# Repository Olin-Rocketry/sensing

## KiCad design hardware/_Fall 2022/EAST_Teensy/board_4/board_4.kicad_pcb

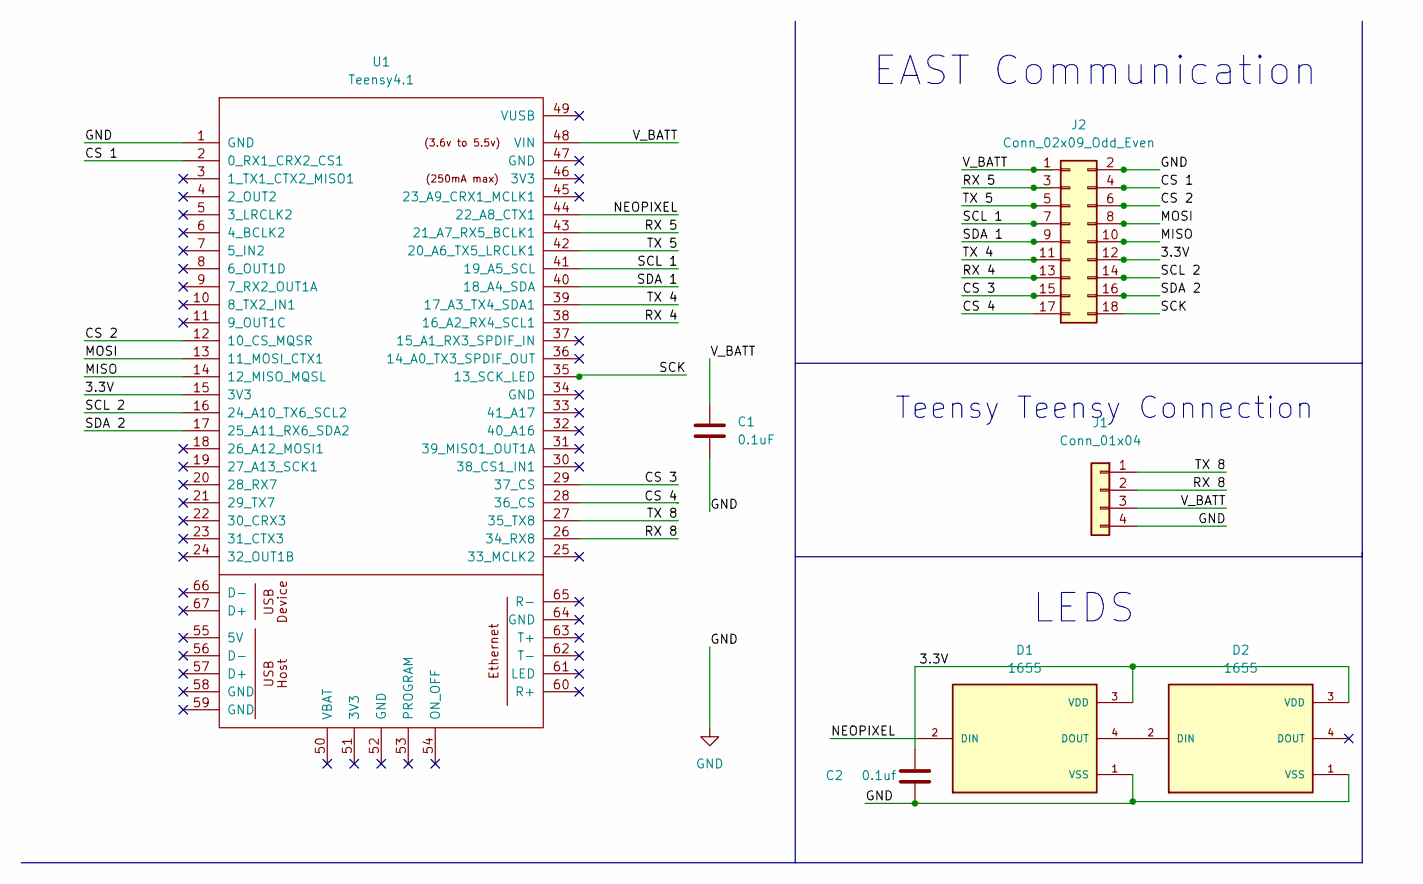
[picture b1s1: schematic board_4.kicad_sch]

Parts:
C1: 0.1uF; C_0603_1608Metric
C2: 0.1uf; C_0603_1608Metric
D1, D2: 1655; LED_1655; PARTREV 01
J1: Conn_01x04; JST_PH_S4B-PH-K_1x04_P2.00mm_Horizontal
J2: Conn_02x09_Odd_Even; PinHeader_2x09_P2.54mm_Vertical
U1: Teensy4.1; Teensy41

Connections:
/3.3V: C2.2, D1.3 (VDD), D2.3 (VDD), J2.12, U1.15 (3V3)
/CS 1: J2.4, U1.2 (0_RX1_CRX2_CS1)
/CS 2: J2.6, U1.12 (10_CS_MQSR)
/CS 3: J2.15, U1.29 (37_CS)
/CS 4: J2.17, U1.28 (36_CS)
/MISO: J2.10, U1.14 (12_MISO_MQSL)
/MOSI: J2.8, U1.13 (11_MOSI_CTX1)
/NEOPIXEL: D1.2 (DIN), U1.44 (22_A8_CTX1)
/RX 4: J2.13, U1.38 (16_A2_RX4_SCL1)
/RX 5: J2.3, U1.43 (21_A7_RX5_BCLK1)
/RX 8: J1.2, U1.26 (34_RX8)
/SCK: J2.18, U1.35 (13_SCK_LED)
/SCL 1: J2.7, U1.41 (19_A5_SCL)
/SCL 2: J2.14, U1.16 (24_A10_TX6_SCL2)
/SDA 1: J2.9, U1.40 (18_A4_SDA)
/SDA 2: J2.16, U1.17 (25_A11_RX6_SDA2)
/TX 4: J2.11, U1.39 (17_A3_TX4_SDA1)
/TX 5: J2.5, U1.42 (20_A6_TX5_LRCLK1)
/TX 8: J1.1, U1.27 (35_TX8)
/V_BATT: C1.1, J1.3, J2.1, U1.48 (VIN)
GND: C1.2, C2.1, D1.1 (VSS), D2.1 (VSS), J1.4, J2.2, U1.1 (GND)
unnamed: D1.4 (DOUT), D2.2 (DIN)

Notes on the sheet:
LEDS
Teensy Teensy Connection
EAST Communication

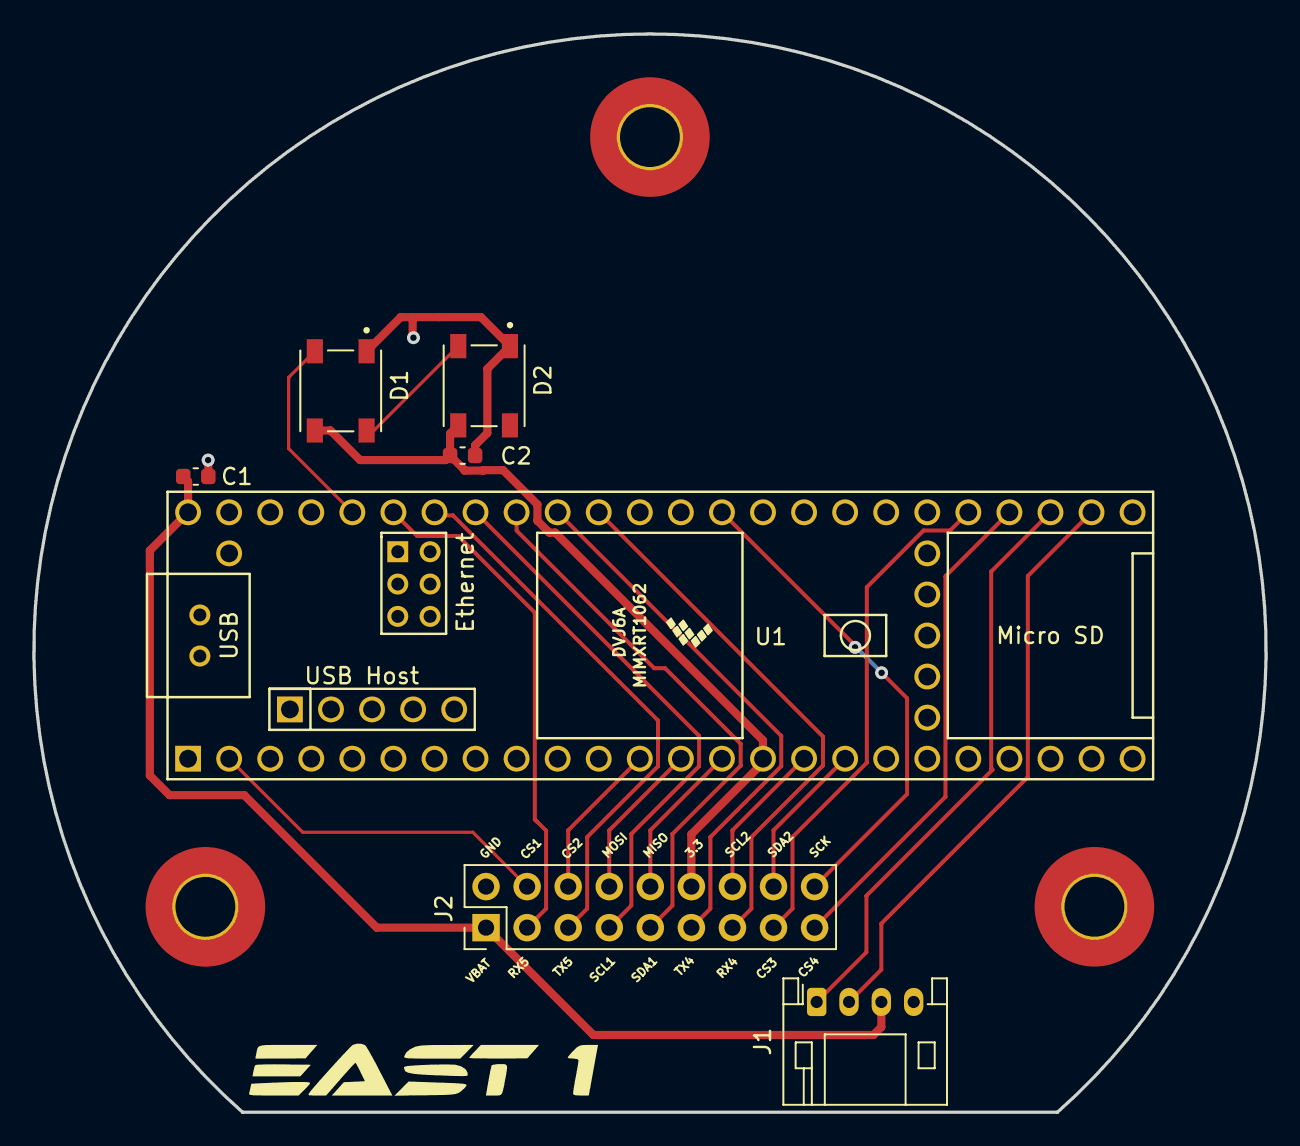
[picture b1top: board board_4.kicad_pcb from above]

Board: 2 copper layers, 76.2 x 66.7 mm, 7 parts (0 on the bottom side), 22 nets.

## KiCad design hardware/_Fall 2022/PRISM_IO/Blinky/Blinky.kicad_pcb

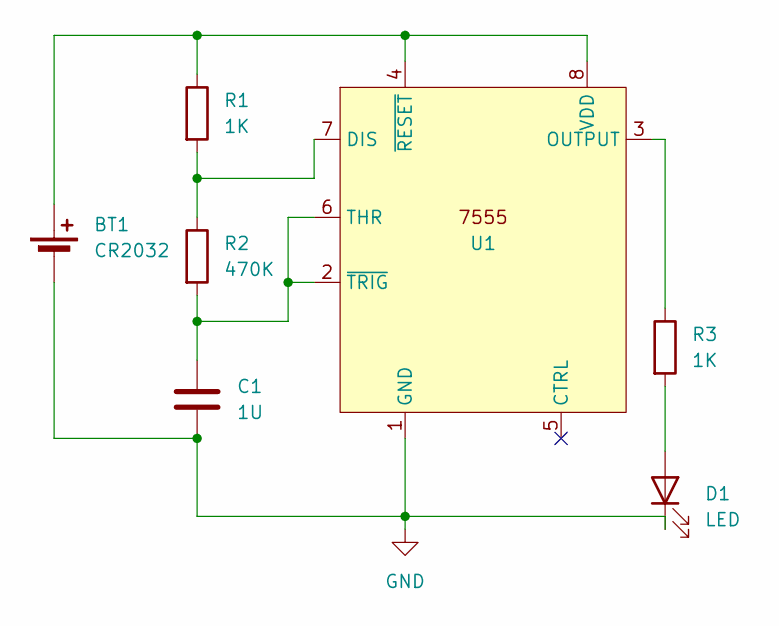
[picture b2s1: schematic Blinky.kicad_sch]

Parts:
BT1: CR2032; S8211-46R
C1: 1U; C_0805_2012Metric_Pad1.18x1.45mm_HandSolder
D1: LED; LED_0805_2012Metric_Pad1.15x1.40mm_HandSolder
R1, R3: 1K; R_0805_2012Metric_Pad1.20x1.40mm_HandSolder
R2: 470K; R_0805_2012Metric_Pad1.20x1.40mm_HandSolder
U1: SOIC-8_3.9x4.9mm_P1.27mm

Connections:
GND: BT1.2 (-), C1.2, D1.1 (K), U1.1 (GND)
unnamed: BT1.1 (+), R1.1, U1.4 (~RESET), U1.8 (VDD)
unnamed: D1.2 (A), R3.2
unnamed: R1.2, R2.1, U1.7 (DIS)
unnamed: R3.1, U1.3 (OUTPUT)
unnamed: C1.1, R2.2, U1.2 (~TRIG), U1.6 (THR)

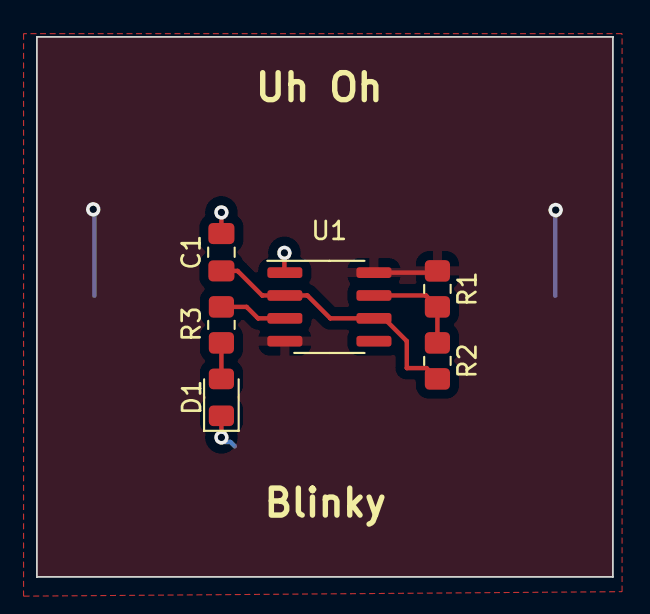
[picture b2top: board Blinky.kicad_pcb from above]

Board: 2 copper layers, 32.0 x 30.0 mm, 7 parts (1 on the bottom side), 6 nets.

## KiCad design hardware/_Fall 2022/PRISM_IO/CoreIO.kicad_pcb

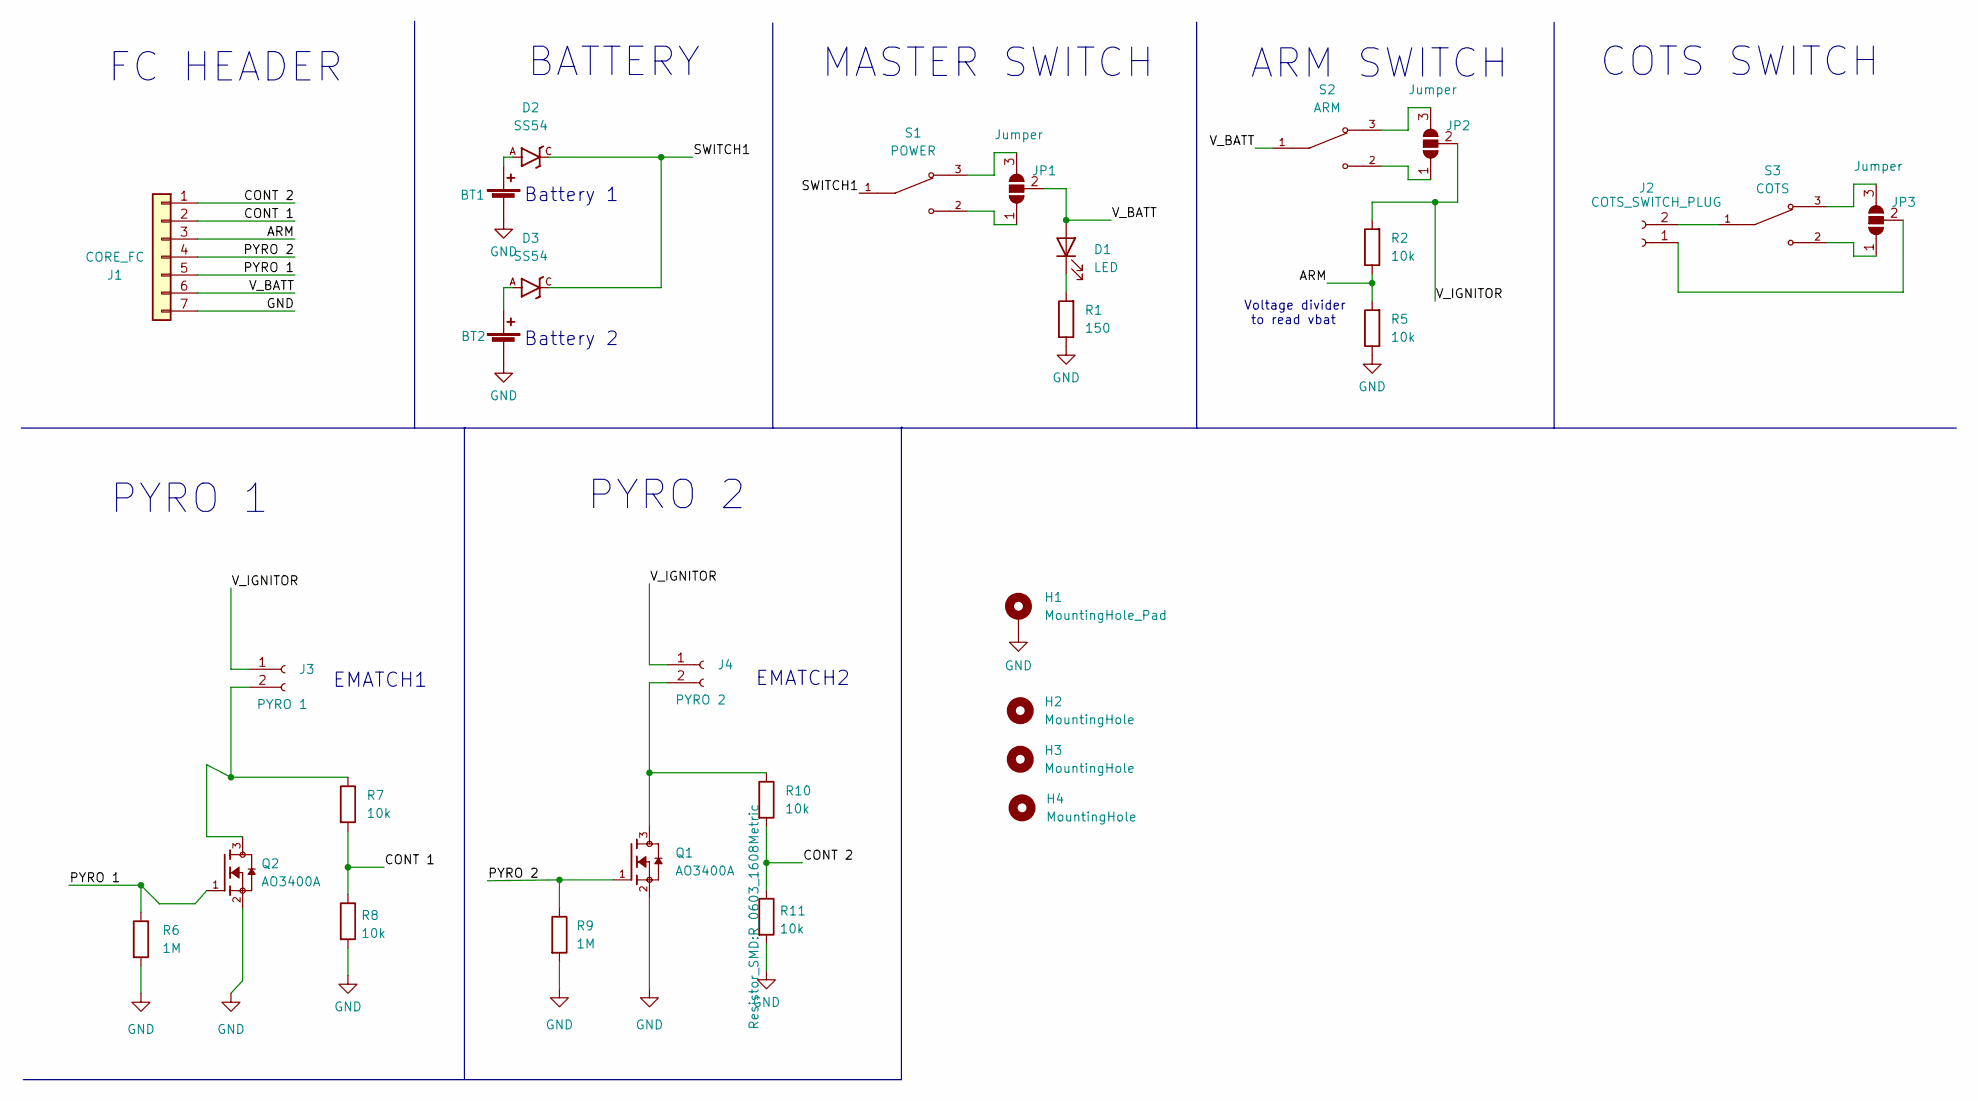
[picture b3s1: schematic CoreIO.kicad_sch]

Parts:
BT1, BT2: JST_SFH_SM02B-SFHRS-TF_02x1.80mm_Angled
D1: LED; LED_0603_1608Metric
D2, D3: SS54; DO-214AC
H1: MountingHole_Pad; MountingHole_3.2mm_M3_DIN965_Pad_TopBottom
H2, H3, H4: MountingHole; MountingHole_3.2mm_M3_DIN965_Pad_TopBottom
J1: CORE_FC; JST_PH_S7B-PH-K_1x07_P2.00mm_Horizontal
J2: COTS_SWITCH_PLUG; JST_PH_S2B-PH-K_1x02_P2.00mm_Horizontal
J3: PYRO 1; JST_SFH_SM02B-SFHRS-TF_02x1.80mm_Angled
J4: PYRO 2; JST_SFH_SM02B-SFHRS-TF_02x1.80mm_Angled
JP1, JP2, JP3: Jumper; SolderJumper-3_P1.3mm_Open_Pad1.0x1.5mm_NumberLabels
Q1, Q2: AO3400A; SOT95P280X125-3N; PARTREV L
R1: 150; R_0603_1608Metric
R2, R5, R7, R8, R10, R11: 10k; R_0603_1608Metric
R6, R9: 1M; R_0603_1608Metric
S1: POWER; SW_D2F-01F; PARTREV B036-E1-12
S2: ARM; SW_D2F-01F; PARTREV B036-E1-12
S3: COTS; SW_D2F-01F; PARTREV B036-E1-12

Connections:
/ARM: J1.3, R2.1, R5.2
/CONT 1: J1.2, R7.2, R8.1
/CONT 2: J1.1, R10.2, R11.1
/PYRO 1: J1.5, Q2.1, R6.1
/PYRO 2: J1.4, Q1.1, R9.1
/SWITCH1: D2.C, D3.C, S1.1
/V_BATT: D1.2 (A), J1.6, JP1.2 (C), S2.1
/V_IGNITOR: J3.1, J4.1, JP2.2 (C), R2.2
GND: BT1.2 (-), BT2.2 (-), H1.1, J1.7, Q1.2, Q2.2, R1.1, R5.1, R6.2, R8.2, R9.2, R11.2
unnamed: BT1.1 (+), D2.A
unnamed: BT2.1 (+), D3.A
unnamed: D1.1 (K), R1.2
unnamed: J2.1, JP3.2 (C)
unnamed: J2.2, S3.1
unnamed: J3.2, Q2.3, R7.1
unnamed: J4.2, Q1.3, R10.1
unnamed: JP1.1 (A), S1.2
unnamed: JP1.3 (B), S1.3
unnamed: JP2.1 (A), S2.2
unnamed: JP2.3 (B), S2.3
unnamed: JP3.1 (A), S3.2
unnamed: JP3.3 (B), S3.3

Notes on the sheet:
ARM SWITCH
EMATCH1
PYRO 1
BATTERY
EMATCH2
Voltage divider to read vbat
MASTER SWITCH
PYRO 2
Battery 2
FC HEADER
COTS SWITCH
Battery 1

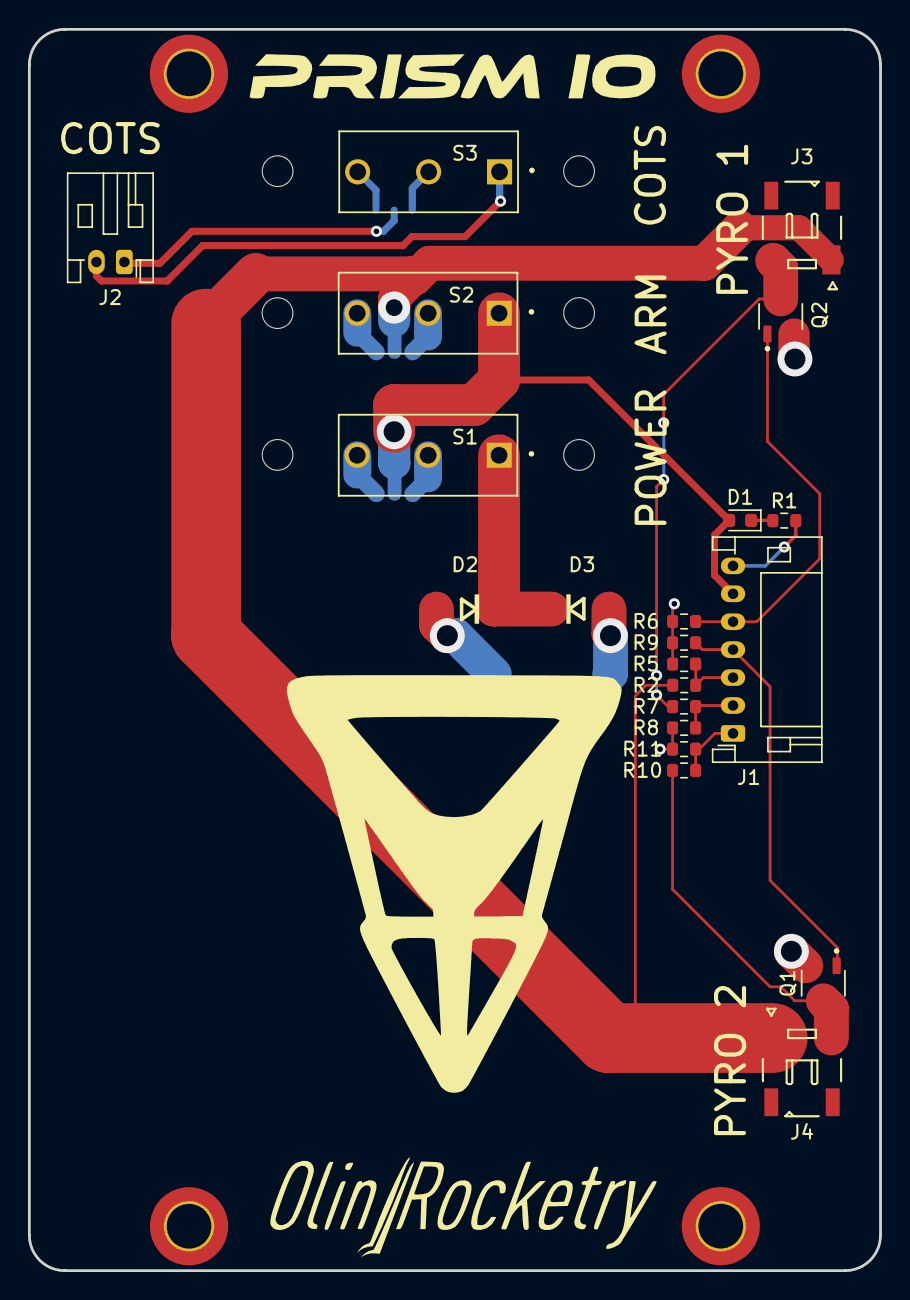
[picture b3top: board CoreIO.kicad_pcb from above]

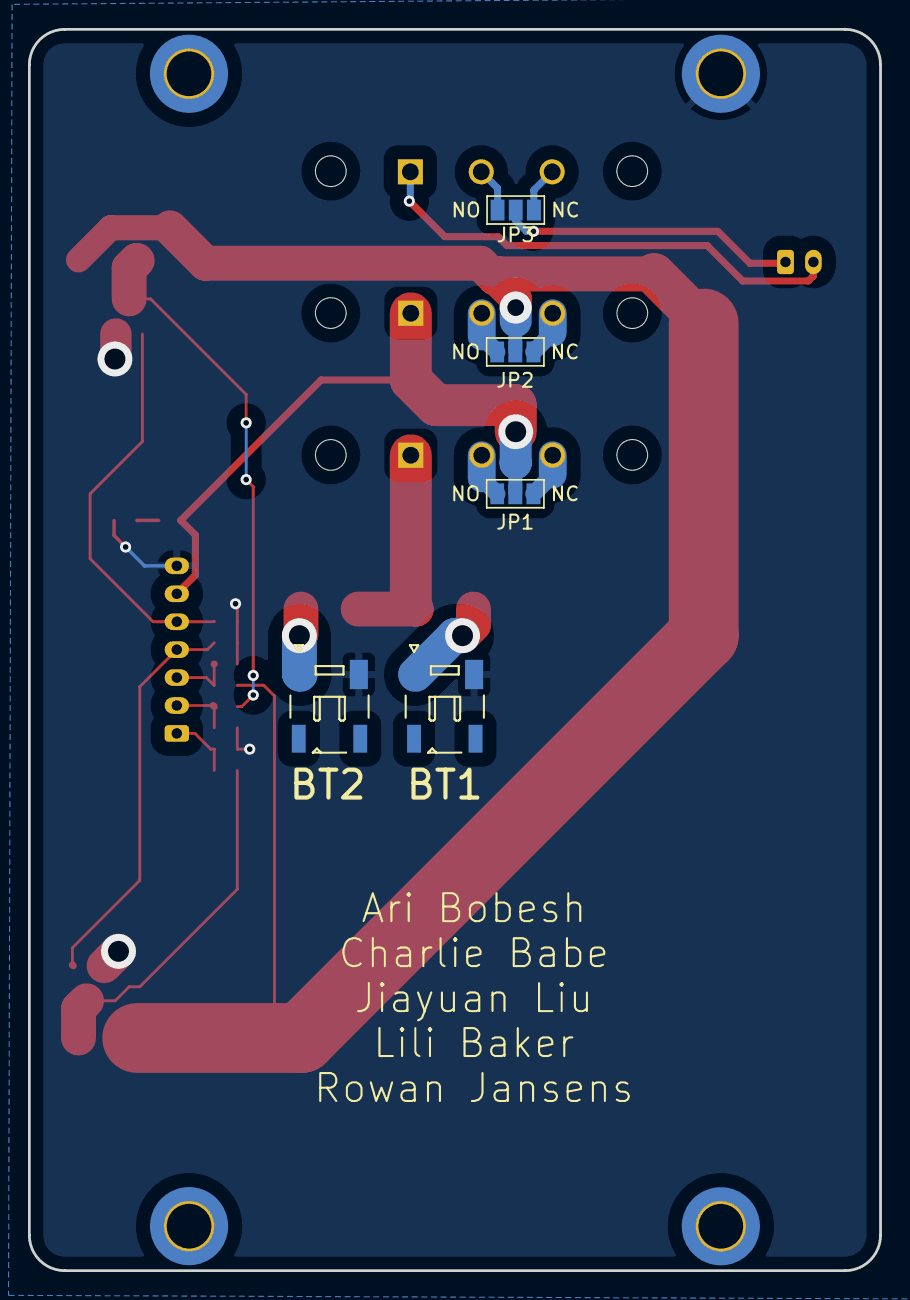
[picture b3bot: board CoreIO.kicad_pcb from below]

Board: 2 copper layers, 61.0 x 88.9 mm, 30 parts (5 on the bottom side), 22 nets.

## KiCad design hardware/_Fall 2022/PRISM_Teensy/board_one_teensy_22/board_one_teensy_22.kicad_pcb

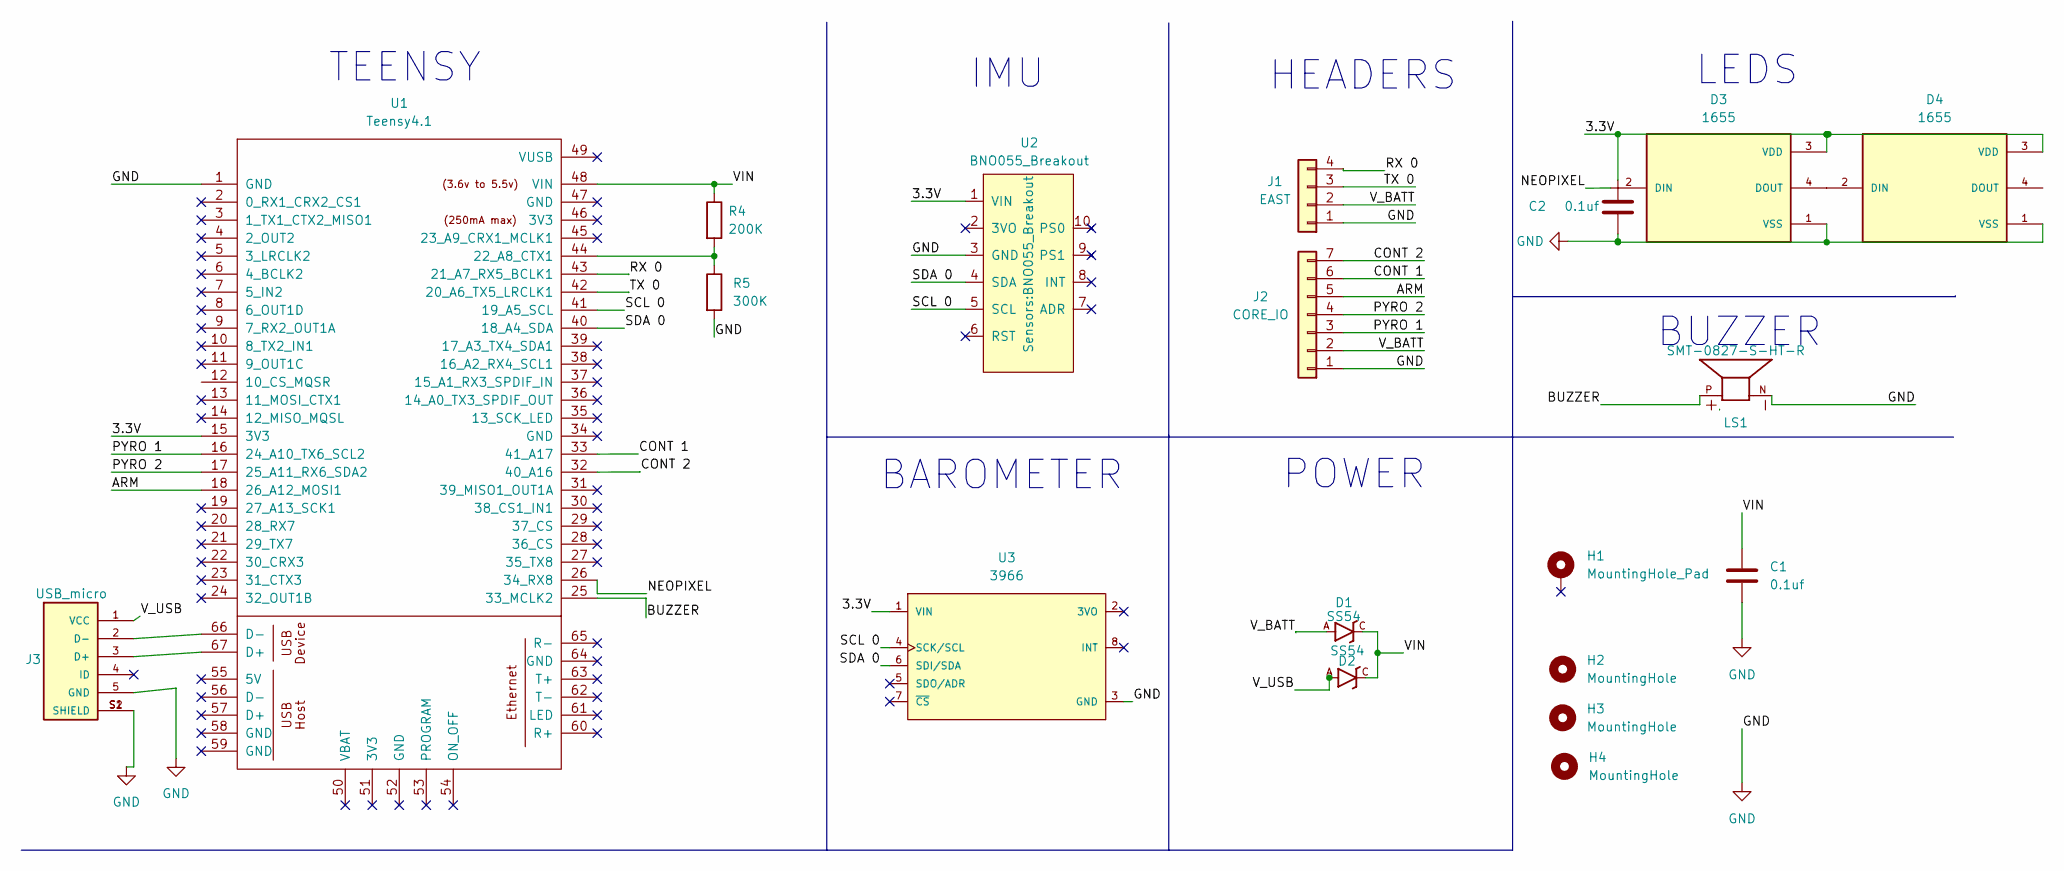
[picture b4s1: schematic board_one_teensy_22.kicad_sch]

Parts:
C1, C2: 0.1uf; C_0603_1608Metric
D1, D2: SS54; DO-214AC
D3, D4: 1655; LED_1655; PARTREV 01
H1: MountingHole_Pad; MountingHole_3.2mm_M3_DIN965_Pad_TopBottom
H2, H3, H4: MountingHole; MountingHole_3.2mm_M3_DIN965_Pad_TopBottom
J1: EAST; JST_PH_S4B-PH-K_1x04_P2.00mm_Horizontal
J2: CORE_IO; JST_PH_S7B-PH-K_1x07_P2.00mm_Horizontal
J3: USB_micro; GCT_USB3131-30-0230-A_REVB
LS1: SMT-0827-S-HT-R; XDCR_SMT-0827-S-HT-R; PARTREV 31/03/20
R4: 200K; R_0603_1608Metric
R5: 300K; R_0603_1608Metric
U1: Teensy4.1; Teensy41
U2: BNO055_Breakout
U3: 3966; Adafruit_Industries-3966-MFG; mouser part number 485-3966; digikey description BMP388 - PRECISION BAROMETRIC PR

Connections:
/3.3V: C2.2, D3.3 (VDD), D4.3 (VDD), U1.15 (3V3), U2.1 (VIN), U3.1 (VIN)
/ARM: J2.5, U1.18 (26_A12_MOSI1)
/BUZZER: LS1.P, U1.25 (33_MCLK2)
/CONT 1: J2.6, U1.33 (41_A17)
/CONT 2: J2.7, U1.32 (40_A16)
/NEOPIXEL: D3.2 (DIN), U1.26 (34_RX8)
/PYRO 1: J2.3, U1.16 (24_A10_TX6_SCL2)
/PYRO 2: J2.4, U1.17 (25_A11_RX6_SDA2)
/RX 0: J1.4, U1.43 (21_A7_RX5_BCLK1)
/SCL 0: U1.41 (19_A5_SCL), U2.5 (SCL), U3.4 (SCK/SCL)
/SDA 0: U1.40 (18_A4_SDA), U2.4 (SDA), U3.6 (SDI/SDA)
/TX 0: J1.3, U1.42 (20_A6_TX5_LRCLK1)
/VIN: C1.1, D1.C, D2.C, R4.1, U1.48 (VIN)
/V_BATT: D1.A, J1.2, J2.2
/V_USB: D2.A, J3.1 (VCC)
GND: C1.2, C2.1, D3.1 (VSS), D4.1 (VSS), J1.1, J2.1, J3.5 (GND), J3.S1 (SHIELD), J3.S2 (SHIELD), LS1.N, R5.2, U1.1 (GND), U2.3 (GND), U3.3 (GND)
unnamed: D3.4 (DOUT), D4.2 (DIN)
unnamed: J3.2 (D-), U1.66 (D-)
unnamed: J3.3 (D+), U1.67 (D+)
unnamed: R4.2, R5.1, U1.44 (22_A8_CTX1)

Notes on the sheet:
BUZZER
TEENSY
HEADERS
POWER
LEDS
IMU
BAROMETER

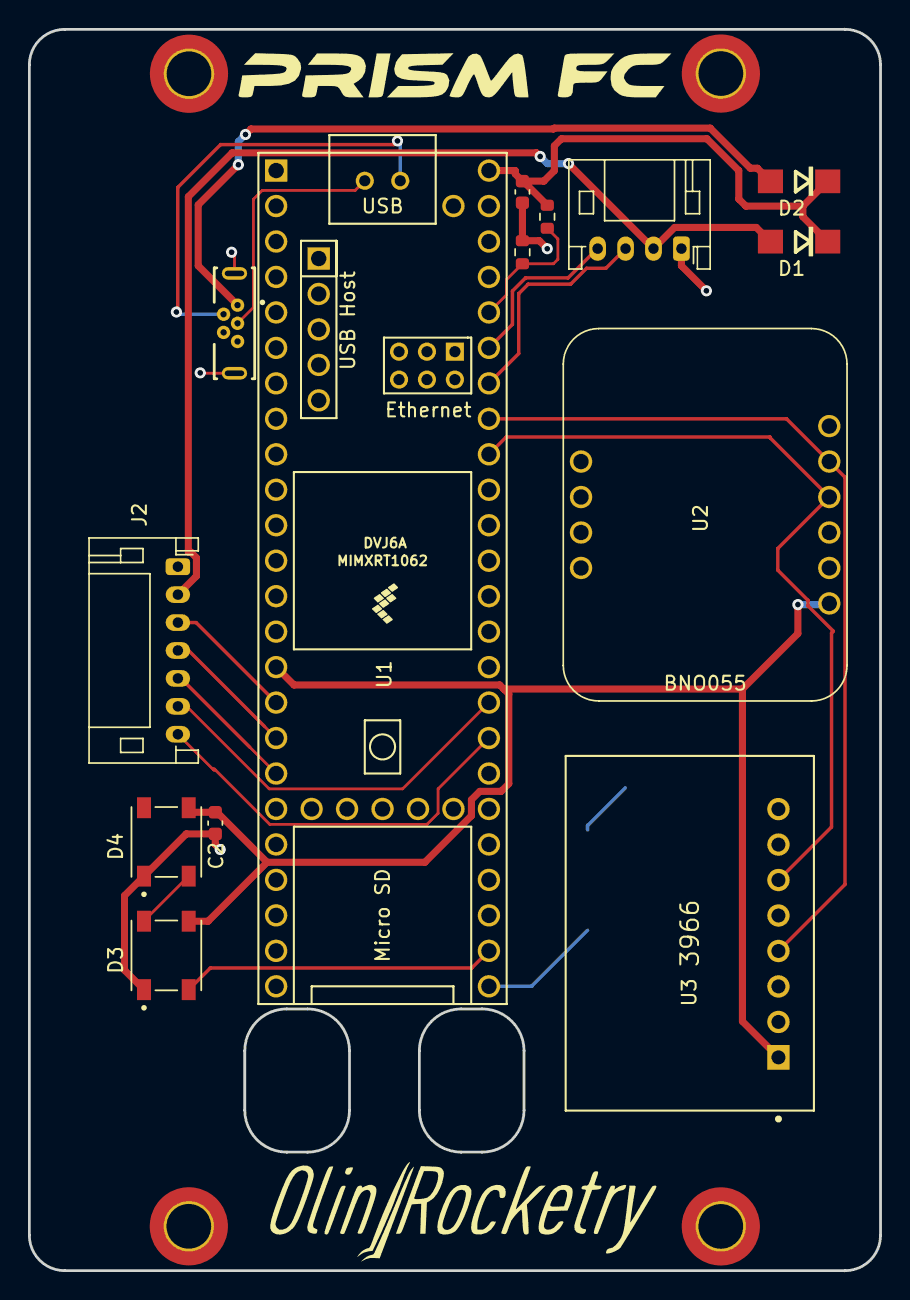
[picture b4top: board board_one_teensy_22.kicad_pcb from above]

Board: 2 copper layers, 61.0 x 88.9 mm, 19 parts (1 on the bottom side), 20 nets.
